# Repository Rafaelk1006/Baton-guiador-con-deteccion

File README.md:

# Baton-guiador-con-deteccion
Repositorio para la presentación del proyecto con sus archivos

En este repositorio se presentan los archivos y el informe que conforman
el conjunto del trabajo realizado para la materia de Taller de Electrónica
por parte un grupo de estudiantes de Mecatronica para realizar el proyecto
Bastón guiador con detección "Don Bastón"

Directorio a la Wiki: https://github.com/Rafaelk1006/Baton-guiador-con-deteccion/wiki

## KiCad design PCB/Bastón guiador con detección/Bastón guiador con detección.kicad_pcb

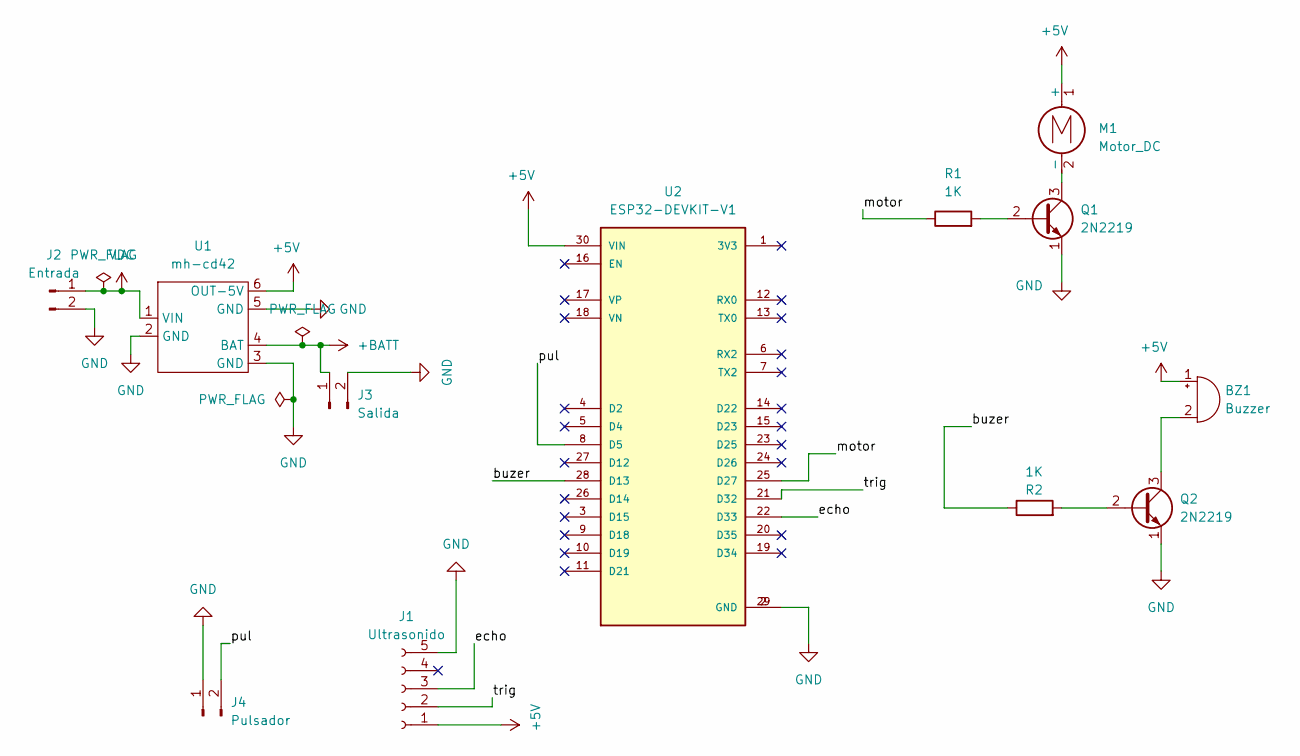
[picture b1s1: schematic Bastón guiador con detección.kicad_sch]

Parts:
BZ1: Buzzer; Buzzer_12x9.5RM7.6
J1: Ultrasonido; Hirose_DF63-5P-3.96DSA_1x05_P3.96mm_Vertical
J2: Entrada; JWT_A3963_1x02_P3.96mm_Vertical
J3: Salida; JWT_A3963_1x02_P3.96mm_Vertical
J4: Pulsador; JWT_A3963_1x02_P3.96mm_Vertical
M1: Motor_DC; PinHeader_1x02_P2.54mm_Horizontal
Q1, Q2: 2N2219; TO-39-3
R1, R2: 1K; R_Axial_DIN0207_L6.3mm_D2.5mm_P10.16mm_Horizontal
U1: mh-cd42
U2: ESP32-DEVKIT-V1; MODULE_ESP32_DEVKIT_V1; PARTREV N/A

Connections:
+5V: BZ1.1 (+), J1.1, M1.1 (+), U1.6 (OUT-5V), U2.30 (VIN)
+BATT: J3.1, U1.4 (BAT)
/buzer: R2.1, U2.28 (D13)
/echo: J1.3, U2.22 (D33)
/motor: R1.1, U2.25 (D27)
/pul: J4.2, U2.8 (D5)
/trig: J1.2, U2.21 (D32)
GND: J1.5, J2.2, J3.2, J4.1, Q1.1 (E), Q2.1 (E), U1.2 (GND), U1.3 (GND), U1.5 (GND), U2.2 (GND), U2.29 (GND)
unnamed: BZ1.2 (-), Q2.3 (C)
unnamed: M1.2 (-), Q1.3 (C)
unnamed: Q1.2 (B), R1.2
unnamed: Q2.2 (B), R2.2
VDC: J2.1, U1.1 (VIN)

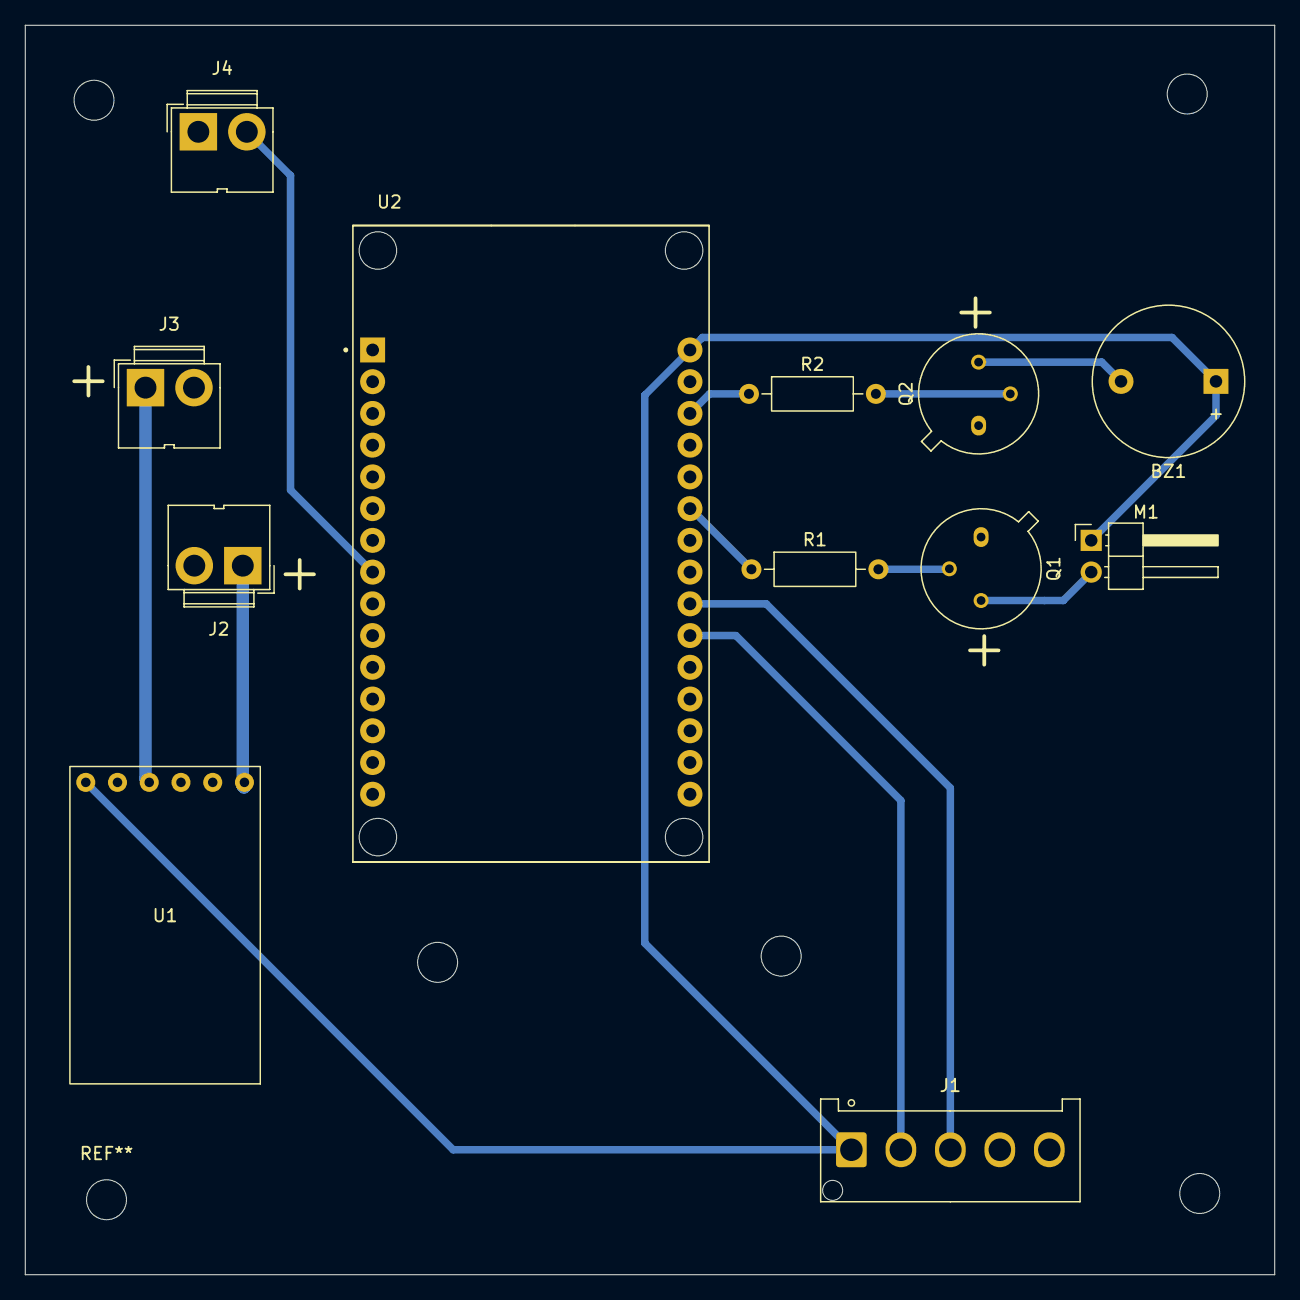
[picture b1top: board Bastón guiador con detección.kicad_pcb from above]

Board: 2 copper layers, 100.0 x 100.0 mm, 12 parts (0 on the bottom side), 13 nets.

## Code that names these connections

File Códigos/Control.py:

from machine import Pin, PWM, time_pulse_us
import time
from time import sleep  

# Pines
TRIG = Pin(32, Pin.OUT)
ECHO = Pin(33, Pin.IN)
BUZZER = PWM(Pin(13), freq=1000, duty=0)
MOTOR = PWM(Pin(27), freq=1000, duty=0)
BUTTON = Pin(5, Pin.IN, Pin.PULL_UP)

# Estado del sistema
sistema_encendido = False 

# Función para medir la distancia
def medir_distancia():
    """Mide la distancia en cm"""
    # Pulso de trigger
    TRIG.off()
    time.sleep_us(2)
    TRIG.on()
    time.sleep_us(10)
    TRIG.off()
    
    # Medir tiempo de respuesta
    try:
        duration = time_pulse_us(ECHO, 1, 30000)
        if duration < 0:
            return None  # Timeout
        
        # Calcular distancia (velocidad sonido = 343 m/s)
        distance = (duration * 0.034) / 2
        return distance
    except:
        return None

# Función para leer el botón con debounce
def leer_boton():
    """Lee el estado del botón y cambia el estado del sistema"""
    global sistema_encendido
    
    # Si el botón está presionado (valor 0 porque usa PULL_UP)
    if BUTTON.value() == 0:
        if not sistema_encendido:
            sistema_encendido = True
            print("=== Sistema ACTIVADO ===")
        sleep(0.05)  # Debounce simple
    else:
        if sistema_encendido:
            sistema_encendido = False
            print("=== Sistema DESACTIVADO ===")
            # Apagar salidas cuando se desactiva
            BUZZER.duty(0)
            MOTOR.duty(0)
def actualizar_salida(distancia):
    # ← AGREGADO: Validación para evitar el error
    if distancia is None:
        print("Error: Lectura de sensor inválida")
        BUZZER.duty(0)
        MOTOR.duty(0)
        return
    
    if distancia < 50:  # Cerquita
        BUZZER.duty(512)
        BUZZER.freq(2000)  # Frecuencia alta
        MOTOR.duty(800)    # Vibración fuerte
    elif distancia < 130:  # Medio- medio
        BUZZER.duty(256)
        BUZZER.freq(1000)  # Frecuencia media
        MOTOR.duty(400)    # Vibración media
    else:  # Muy lejos
        BUZZER.duty(0)
        MOTOR.duty(0)    # Vibración suave

# Bucle principal
while True:
    # Leer el estado del botón
    leer_boton()
    
    if sistema_encendido:
        distancia = medir_distancia()
        print("Distancia: ", distancia)
        actualizar_salida(distancia)
    else:
        # Asegurar que las salidas estén apagadas cuando el sistema está inactivo
        BUZZER.duty(0)
        MOTOR.duty(0)
    
    sleep(0.1)

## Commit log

2025-07-17 Actualización README
    Agregando descripción
2025-07-22 Actualización con archivos de proyecto
    Todo con lo que se trabajó
2025-07-23 Nuevas evidencias
    Nuevas evidencias
2025-07-23 Reorganzado
2025-07-23 Archivos fuentes
2025-07-24 Actualización diagrama
